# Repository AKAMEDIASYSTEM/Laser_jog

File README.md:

# Laser_jog
dumb sketch to make a jogwheel for z axis of cheap lasercutter

junkbox 12-detent rotary encoder (outputs 96 ticks per rev, though)
darling little 128x64 SSD1306 OLED screen
easy driver from the strategic reserve

==> Jog wheel controlling the stepper in [this](http://www.lightobject.com/Power-table-bed-kit-for-K40-small-laser-machine-P722.aspx)
==> Simple OLED display of stepper and encoder position

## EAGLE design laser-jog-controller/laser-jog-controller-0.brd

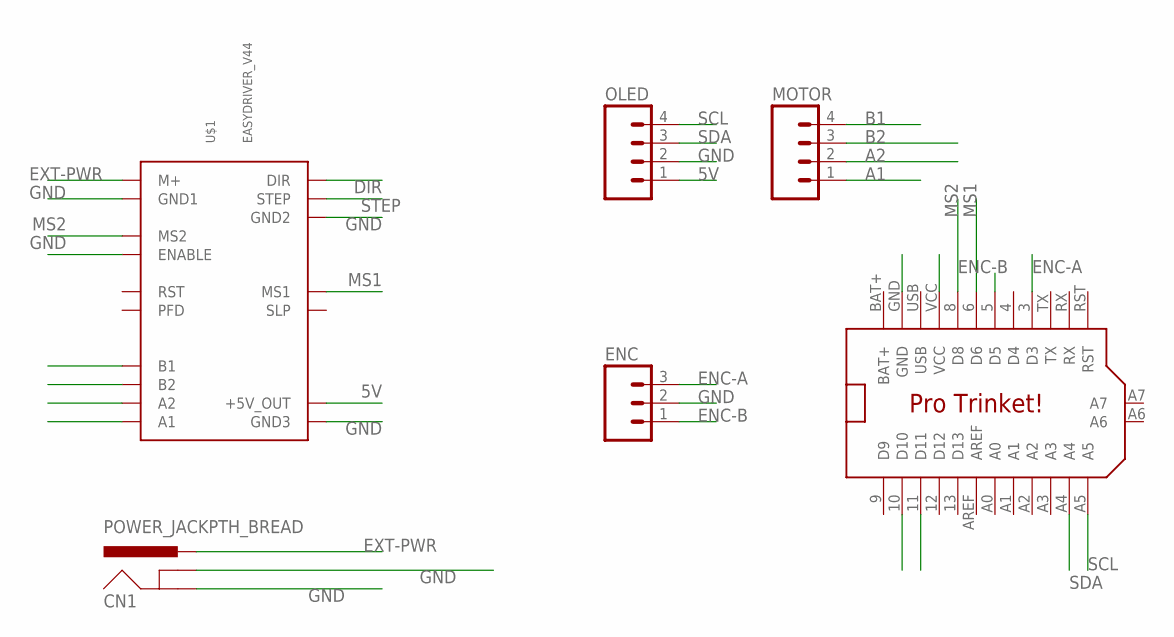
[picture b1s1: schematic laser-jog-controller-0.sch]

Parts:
CN1: POWER_JACKPTH_BREAD; POWER_JACK_PTH_BREAD
ENC: M03LOCK_LONGPADS; 1X03_LOCK_LONGPADS
MOTOR: M04LOCK_LONGPADS; 1X04_LOCK_LONGPADS
OLED: M04LOCK_LONGPADS; 1X04_LOCK_LONGPADS
U$1: EASYDRIVER_V44
U$2: PRO_TRINKET; PROTRINKET

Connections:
5V: OLED.1, U$1.P$11 (+5V_OUT), U$2.VCC
A1: MOTOR.1, U$1.A1
A2: MOTOR.2, U$1.A2
B1: MOTOR.4, U$1.B1
B2: MOTOR.3, U$1.B2
BAT+: U$2.BAT+
DIR: U$1.DIR, U$2.11 (D11)
ENC-A: ENC.3, U$2.3 (D3)
ENC-B: ENC.1, U$2.5 (D5)
EXT-PWR: CN1.PWR, U$1.M+
GND: CN1.GND, CN1.GNDBREAK, ENC.2, OLED.2, U$1.ENABLE, U$1.GND1, U$1.GND2, U$1.GND3, U$2.GND
MS1: U$1.MS1, U$2.6 (D6)
MS2: U$1.MS2, U$2.8 (D8)
SCL: OLED.4, U$2.A5
SDA: OLED.3, U$2.A4
STEP: U$1.STEP, U$2.10 (D10)
USB: U$2.USB

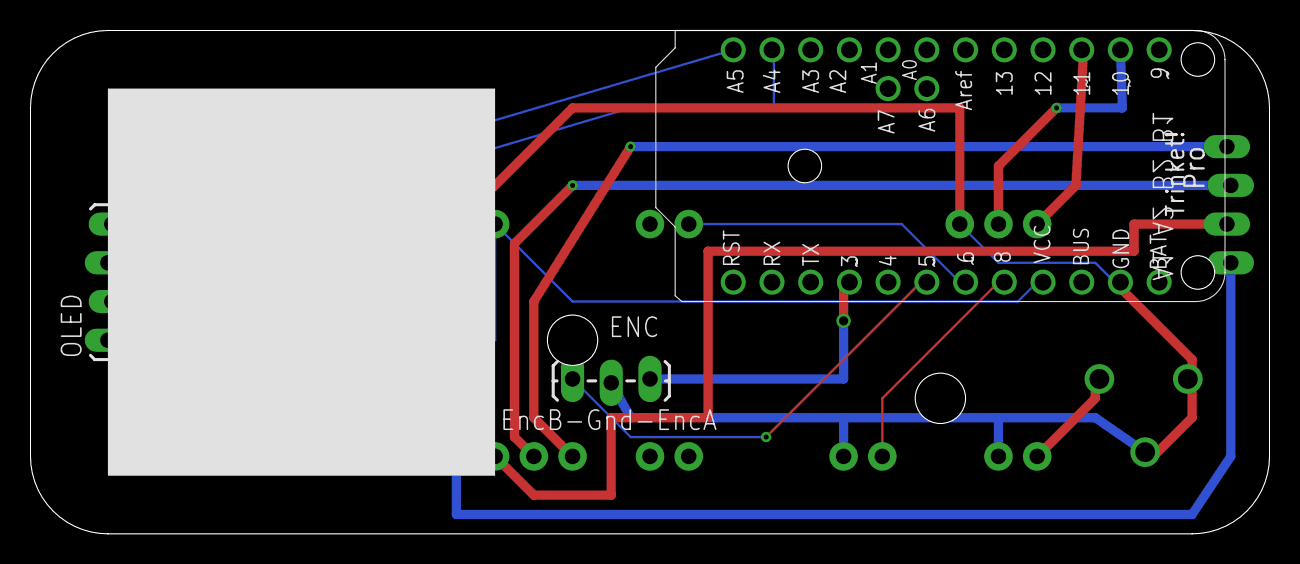
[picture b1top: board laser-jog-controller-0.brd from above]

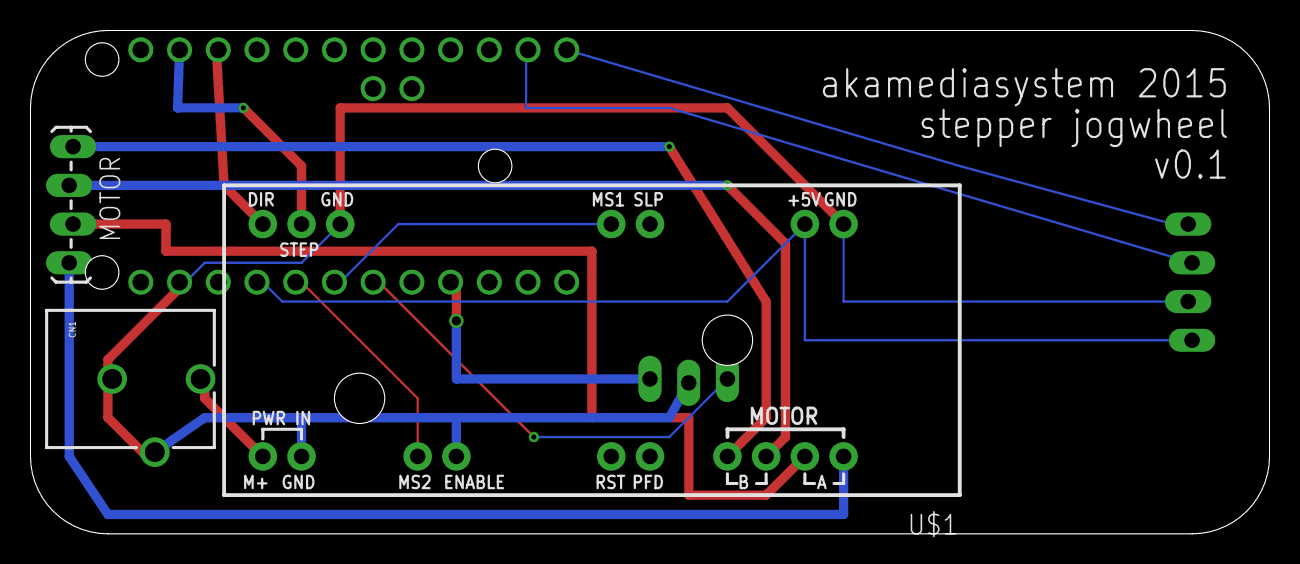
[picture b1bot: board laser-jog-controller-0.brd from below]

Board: 2 copper layers, 81.3 x 33.0 mm, 6 parts (3 on the bottom side), 15 nets.

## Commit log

2015-05-31 first up, running ok
2015-05-31 cleanup
2015-08-30 added perhaps-superfluous connections between the microstep pins and the trinket (because there was extra space)
2015-08-30 added eagle files, untested board tho - just a design at this point
2015-08-31 did gitignore wrong i guess
2015-09-13 updated MS1 and MS2 pin mappings and testing OSH board v0.1

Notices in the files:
parts and their libraries:
SparkFun-Connectors: Licensing: Creative Commons ShareAlike 4.0 International - https://creativecommons.org/licenses/by-sa/4.0
